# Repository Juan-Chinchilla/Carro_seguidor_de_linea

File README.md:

# Carro_seguidor_de_linea
Proyecto en el cual crearemos un carro que sea capas de seguir una linea negra y capas de superar pequeños percances que se le presenten

Proyecto  Hard-21

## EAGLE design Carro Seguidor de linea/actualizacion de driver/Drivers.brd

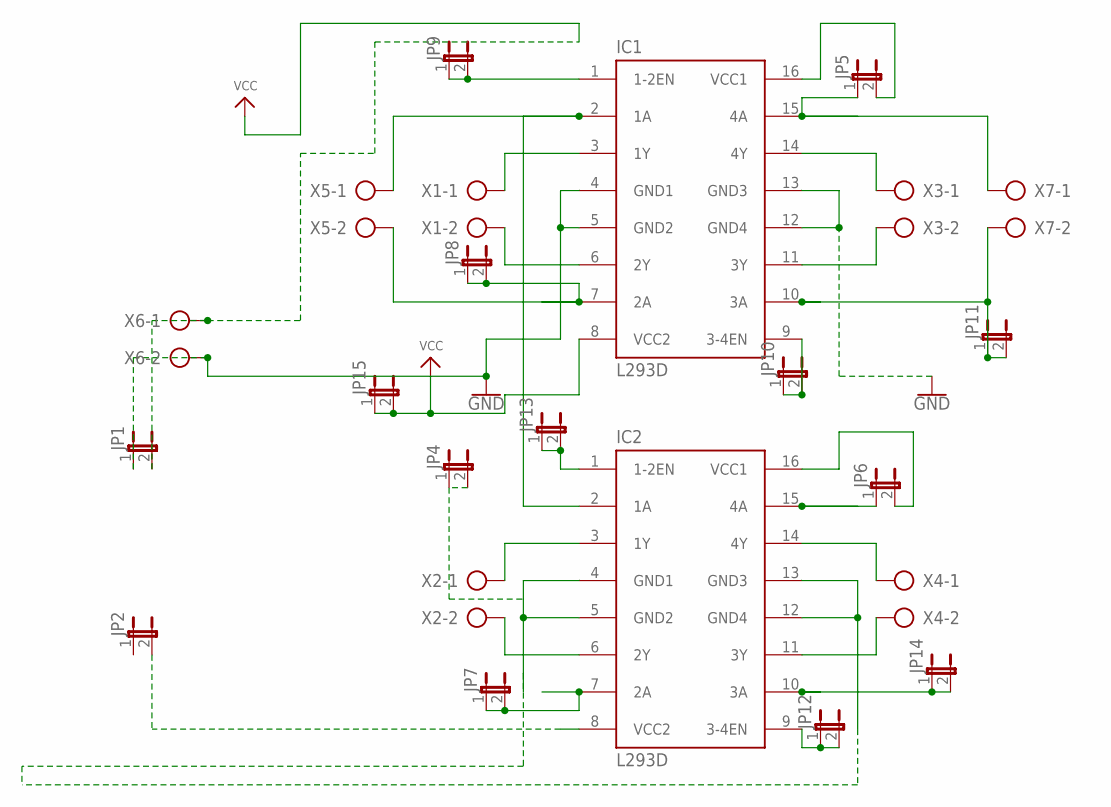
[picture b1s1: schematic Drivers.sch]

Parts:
IC1, IC2: L293D; DIL16
JP1, JP2, JP4, JP5, JP6, JP7, JP8, JP9, JP10, JP11, JP12, JP13, JP14, JP15: JP1E; JP1
X1, X2, X3, X4, X5, X6, X7: AK500/2-H

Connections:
GND: IC1.4 (GND1), IC1.5 (GND2), IC1.12 (GND4), IC1.13 (GND3), JP1.1, X6.2
unnamed: IC2.10 (3A), JP14.1, JP14.2
unnamed: IC2.7 (2A), JP7.1, JP7.2
unnamed: IC1.7 (2A), JP8.1, JP8.2, X5.2
unnamed: IC1.3 (1Y), X1.1
unnamed: IC1.6 (2Y), X1.2
unnamed: IC2.3 (1Y), X2.1
unnamed: IC2.6 (2Y), X2.2
unnamed: IC1.11 (3Y), X3.2
unnamed: IC1.14 (4Y), X3.1
unnamed: IC2.11 (3Y), X4.2
unnamed: IC2.14 (4Y), X4.1
unnamed: IC1.2 (1A), IC2.2 (1A), X5.1
unnamed: IC2.15 (4A), JP6.1
unnamed: IC1.10 (3A), JP11.1, JP11.2, X7.2
unnamed: IC1.1 (1-2EN), JP9.1, JP9.2
unnamed: IC2.8 (VCC2), JP2.2
unnamed: IC2.4 (GND1), IC2.5 (GND2), IC2.12 (GND4), IC2.13 (GND3), JP4.1, JP4.2
unnamed: IC1.15 (4A), JP5.1, X7.1
unnamed: IC1.9 (3-4EN), JP10.1, JP10.2
unnamed: IC2.9 (3-4EN), JP12.1, JP12.2
unnamed: IC2.1 (1-2EN), JP13.1, JP13.2
unnamed: IC2.16 (VCC1), JP6.2
unnamed: IC1.16 (VCC1), JP5.2
VCC: IC1.8 (VCC2), JP1.2, JP15.1, JP15.2, X6.1

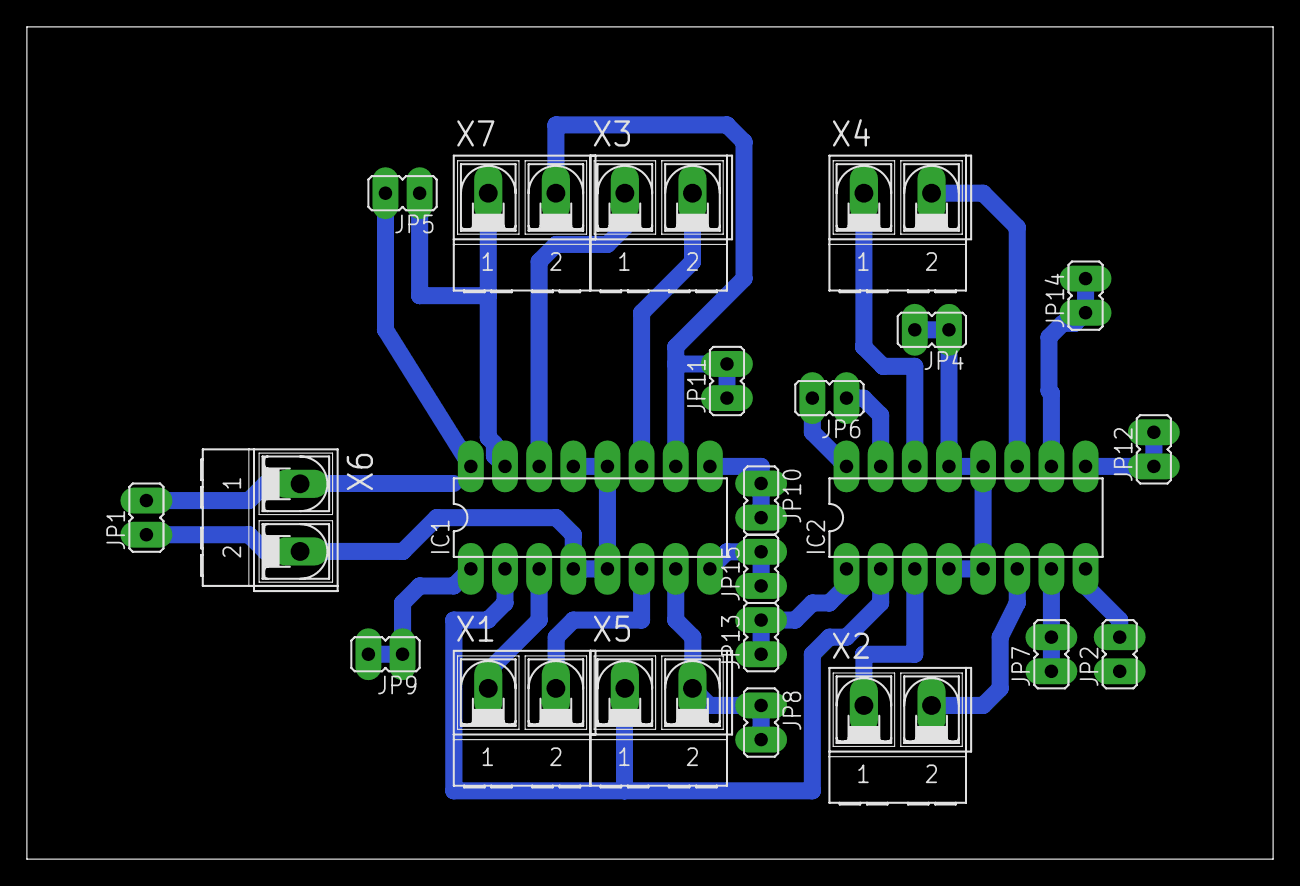
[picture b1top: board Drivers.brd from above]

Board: 2 copper layers, 92.7 x 61.9 mm, 23 parts (0 on the bottom side), 25 nets.

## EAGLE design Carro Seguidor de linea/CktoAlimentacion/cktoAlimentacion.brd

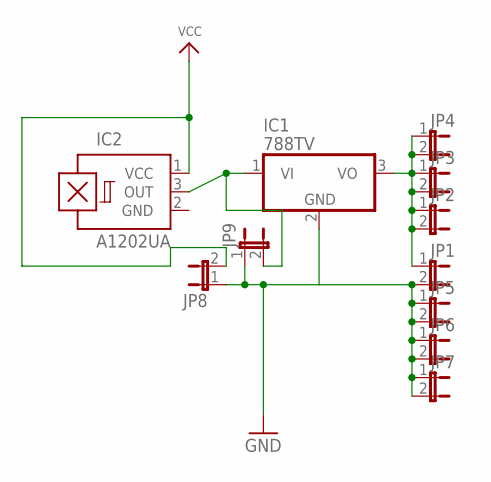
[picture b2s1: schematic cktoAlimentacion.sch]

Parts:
IC1: 788TV; TO220V
IC2: A1202UA; SIP3-UA
JP1, JP2, JP3, JP4, JP5, JP6, JP7, JP8, JP9: JP1E; JP1

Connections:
GND: IC1.2 (GND), IC2.2 (GND), JP1.2, JP5.1, JP5.2, JP6.1, JP6.2, JP7.1, JP7.2, JP8.1, JP9.1
unnamed: IC1.1 (VI), IC2.3 (OUT), JP9.2
unnamed: IC1.3 (VO), JP1.1, JP2.1, JP2.2, JP3.1, JP3.2, JP4.1, JP4.2
VCC: IC2.1 (VCC), JP8.2

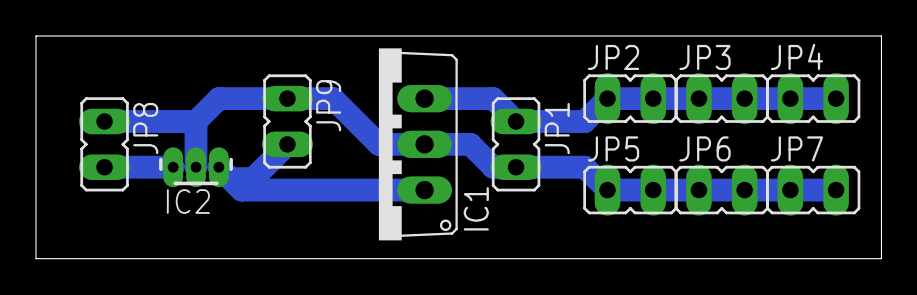
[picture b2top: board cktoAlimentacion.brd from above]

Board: 2 copper layers, 47.0 x 12.4 mm, 11 parts (0 on the bottom side), 4 nets.

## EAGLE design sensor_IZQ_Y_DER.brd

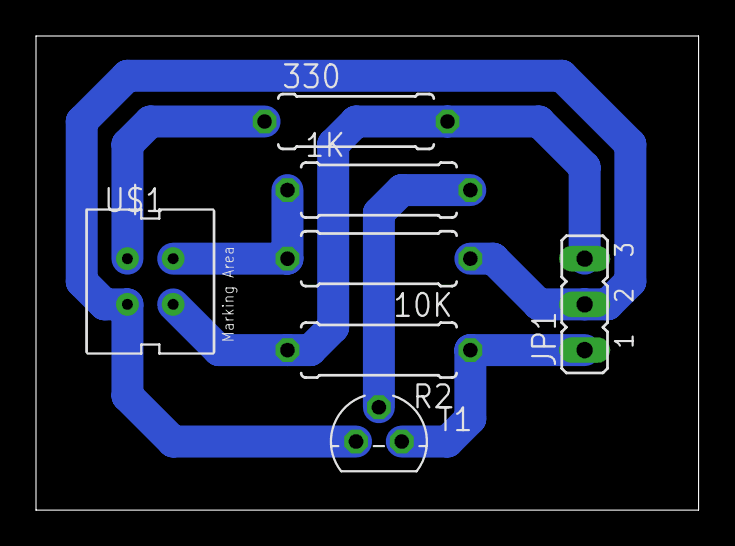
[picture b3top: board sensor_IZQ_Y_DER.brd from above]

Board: 2 copper layers, 36.8 x 26.3 mm, 7 parts (0 on the bottom side), 6 nets.

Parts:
1K, 10K, 330: 0309/10
JP1: JP2
R2: 0309/10
T1: 2N3904; TO92
U$1: CNY70; 4

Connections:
unnamed: 330.2, JP1.3, R2.2, U$1.C
unnamed: 10K.1, JP1.2, T1.3, U$1.K
unnamed: 1K.2, T1.2
unnamed: 1K.1, 10K.2, U$1.E
unnamed: 330.1, U$1.A
unnamed: JP1.1, R2.1, T1.1

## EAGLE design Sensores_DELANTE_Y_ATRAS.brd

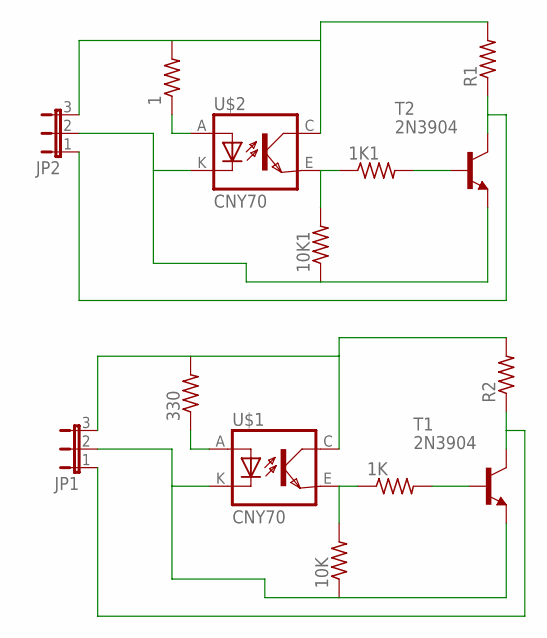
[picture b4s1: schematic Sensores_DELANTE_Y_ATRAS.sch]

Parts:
1, 1K, 1K1, 10K, 10K1, 330: R-US_0309/10; 0309/10
JP1, JP2: JP2E; JP2
R1, R2: R-US_0309/10; 0309/10
T1, T2: 2N3904; TO92
U$1, U$2: CNY70; 4

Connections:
unnamed: 330.2, JP1.3, R2.2, U$1.C (COL)
unnamed: 10K.1, JP1.2, T1.3 (E), U$1.K (C)
unnamed: 1K.2, T1.2 (B)
unnamed: 1K.1, 10K.2, U$1.E (EMI)
unnamed: 330.1, U$1.A
unnamed: JP1.1, R2.1, T1.1 (C)
unnamed: 1.2, JP2.3, R1.2, U$2.C (COL)
unnamed: 10K1.1, JP2.2, T2.3 (E), U$2.K (C)
unnamed: 1K1.2, T2.2 (B)
unnamed: 1K1.1, 10K1.2, U$2.E (EMI)
unnamed: 1.1, U$2.A
unnamed: JP2.1, R1.1, T2.1 (C)

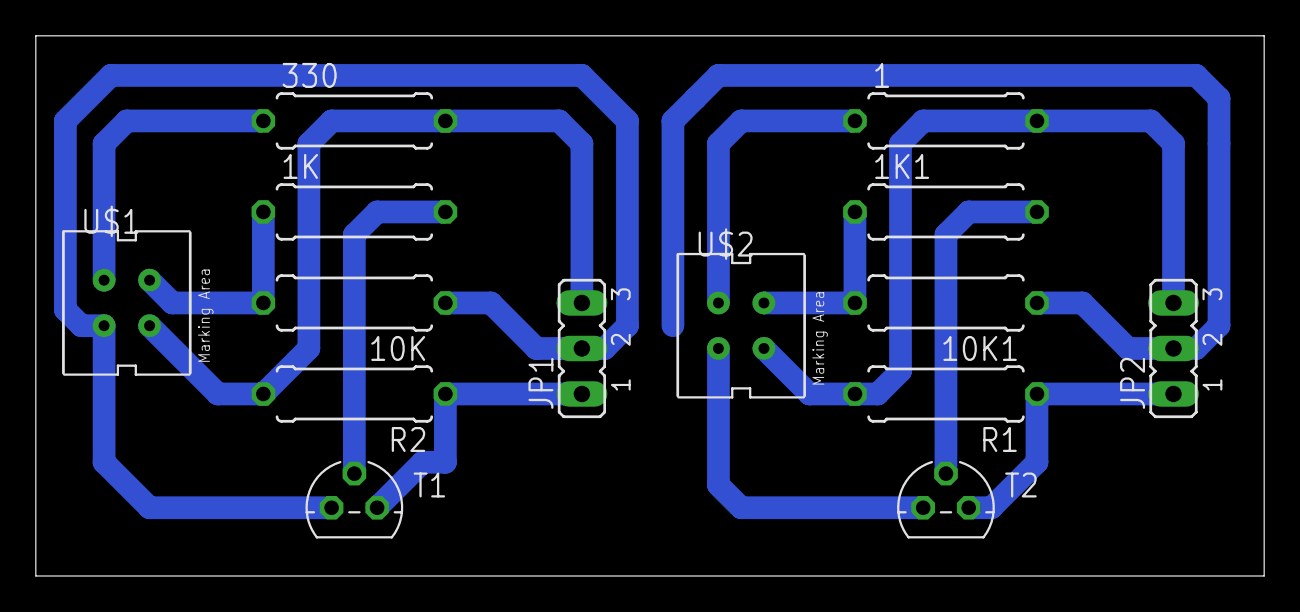
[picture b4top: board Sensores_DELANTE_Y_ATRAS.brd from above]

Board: 2 copper layers, 68.6 x 30.1 mm, 14 parts (0 on the bottom side), 12 nets.

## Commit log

2018-05-19 actualizacion
2018-05-19 Archivos de proyecto
    los archivos de el proyecto del carro seguidor de linea
2018-06-05 Actualización
    los nuevos archivos actualizados del proyecto carro seguidor de linea en el cual sean corregido algunos errores
2018-06-11 Driver y programación para 4 sensores.
    en esta actualización hemos subido una mejora al los puentes H, ya que tenias problemas con la anterior.
    A su ves la programación para 4 sensores(funcional)... pensamos agregar los 6 sensores. si desdimos agregarlos
    espere posible actualización de código.
2018-06-12 actualización: Programación final
    en esta programacion a diferencia de la anteriro subida, esta es para 6 sensores, funcional.
2018-06-13 Paper de proyecto

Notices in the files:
parts and their libraries:
SparkFun-PowerSymbols: Licensing: Creative Commons ShareAlike 4.0 International - https://creativecommons.org/licenses/by-sa/4.0
